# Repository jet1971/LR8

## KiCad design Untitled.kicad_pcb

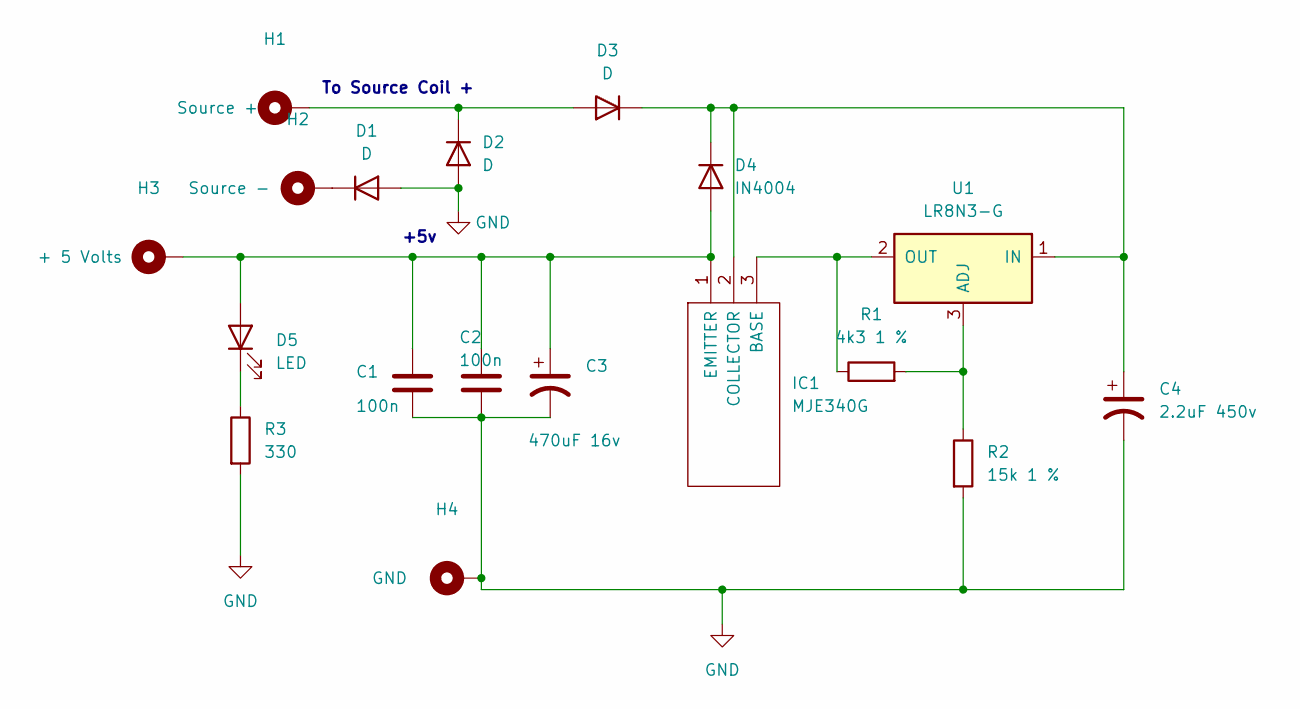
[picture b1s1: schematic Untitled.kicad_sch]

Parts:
C1, C2: 100n; C_Disc_D6.0mm_W2.5mm_P5.00mm
C3: 470uF 16v; C_Radial_D10.0mm_H16.0mm_P5.00mm
C4: 2.2uF 450v; C_Radial_D10.0mm_H12.5mm_P5.00mm
D1, D2, D3: D; D_DO-41_SOD81_P10.16mm_Horizontal
D4: IN4004; D_DO-41_SOD81_P10.16mm_Horizontal
D5: LED; LED_D3.0mm
H1: Source +; MountingHole_2.2mm_M2_DIN965_Pad
H2: Source -; MountingHole_2.2mm_M2_DIN965_Pad
H3: + 5 Volts; MountingHole_2.2mm_M2_DIN965_Pad
H4: GND; MountingHole_2.2mm_M2_DIN965_Pad
IC1: MJE340G; TO229P300X760X1364-3P; Manufacturer_Part_Number MJE340G; Mouser Part Number 863-MJE340G
R1: 4k3 1 %; R_Axial_DIN0309_L9.0mm_D3.2mm_P12.70mm_Horizontal
R2: 15k 1 %; R_Axial_DIN0309_L9.0mm_D3.2mm_P12.70mm_Horizontal
R3: 330; R_Axial_DIN0204_L3.6mm_D1.6mm_P7.62mm_Horizontal
U1: LR8N3-G; TO-92_Inline

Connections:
GND: C1.2, C2.2, C3.2, C4.2, D1.2 (A), D2.2 (A), H4.1, R2.2, R3.2
unnamed: C1.1, C2.1, C3.1, D4.2 (A), D5.2 (A), H3.1, IC1.1 (EMITTER)
unnamed: C4.1, D3.1 (K), D4.1 (K), IC1.2 (COLLECTOR), U1.1 (IN)
unnamed: D1.1 (K), H2.1
unnamed: D2.1 (K), D3.2 (A), H1.1
unnamed: D5.1 (K), R3.1
unnamed: IC1.3 (BASE), R1.1, U1.2 (OUT)
unnamed: R1.2, R2.1, U1.3 (ADJ)

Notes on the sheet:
+5v
To Source Coil +

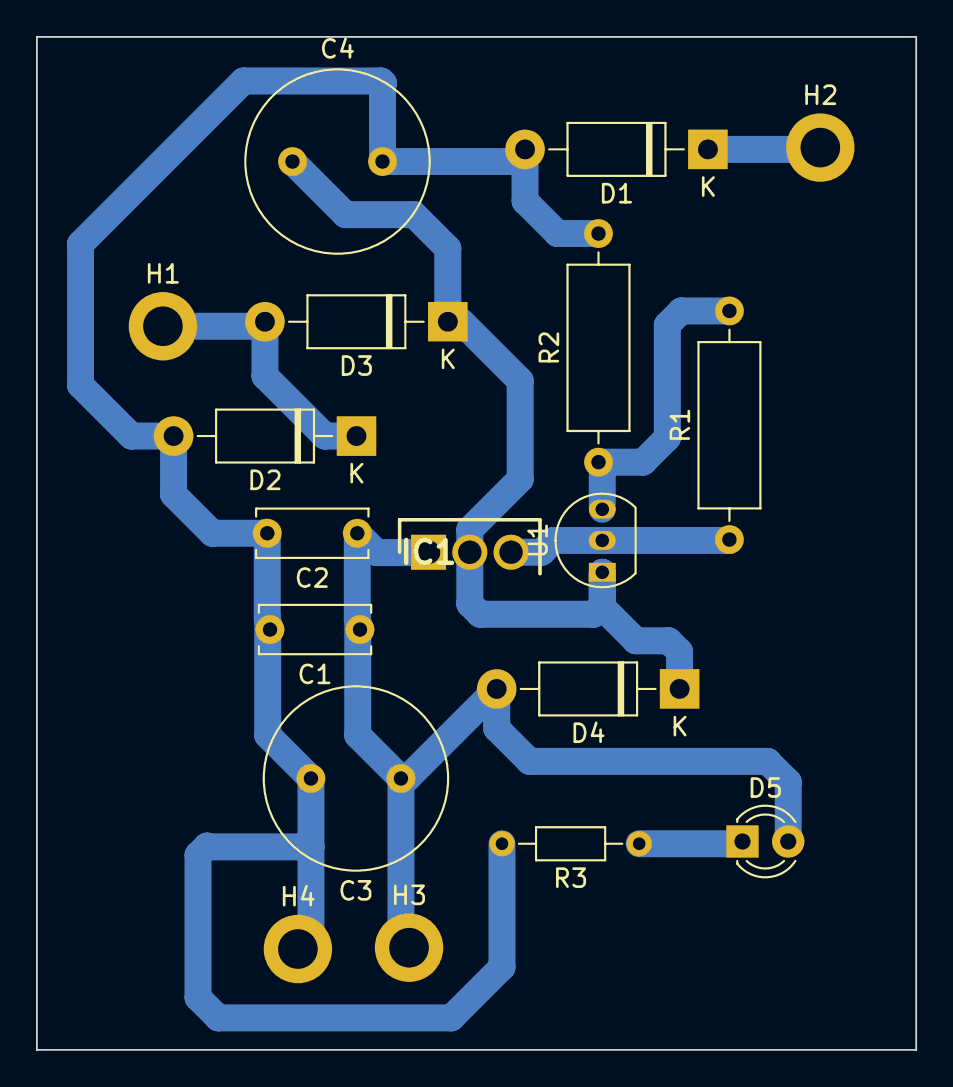
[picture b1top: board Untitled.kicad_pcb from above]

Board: 2 copper layers, 48.8 x 56.3 mm, 18 parts (0 on the bottom side), 8 nets.

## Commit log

2022-09-03 Cap added
